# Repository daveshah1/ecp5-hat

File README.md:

# ecp5-hat

This board adds 64MB of SDRAM, 4-bit RGB+bright VGA output and a USB host connector to the Lattice [ECP5 Versa](http://www.latticesemi.com/Products/DevelopmentBoardsAndKits/ECP5VersaDevelopmentKit.aspx)
and [ECP5 Evaluation Board](http://www.latticesemi.com/en/Products/DevelopmentBoardsAndKits/ECP5EvaluationBoard)

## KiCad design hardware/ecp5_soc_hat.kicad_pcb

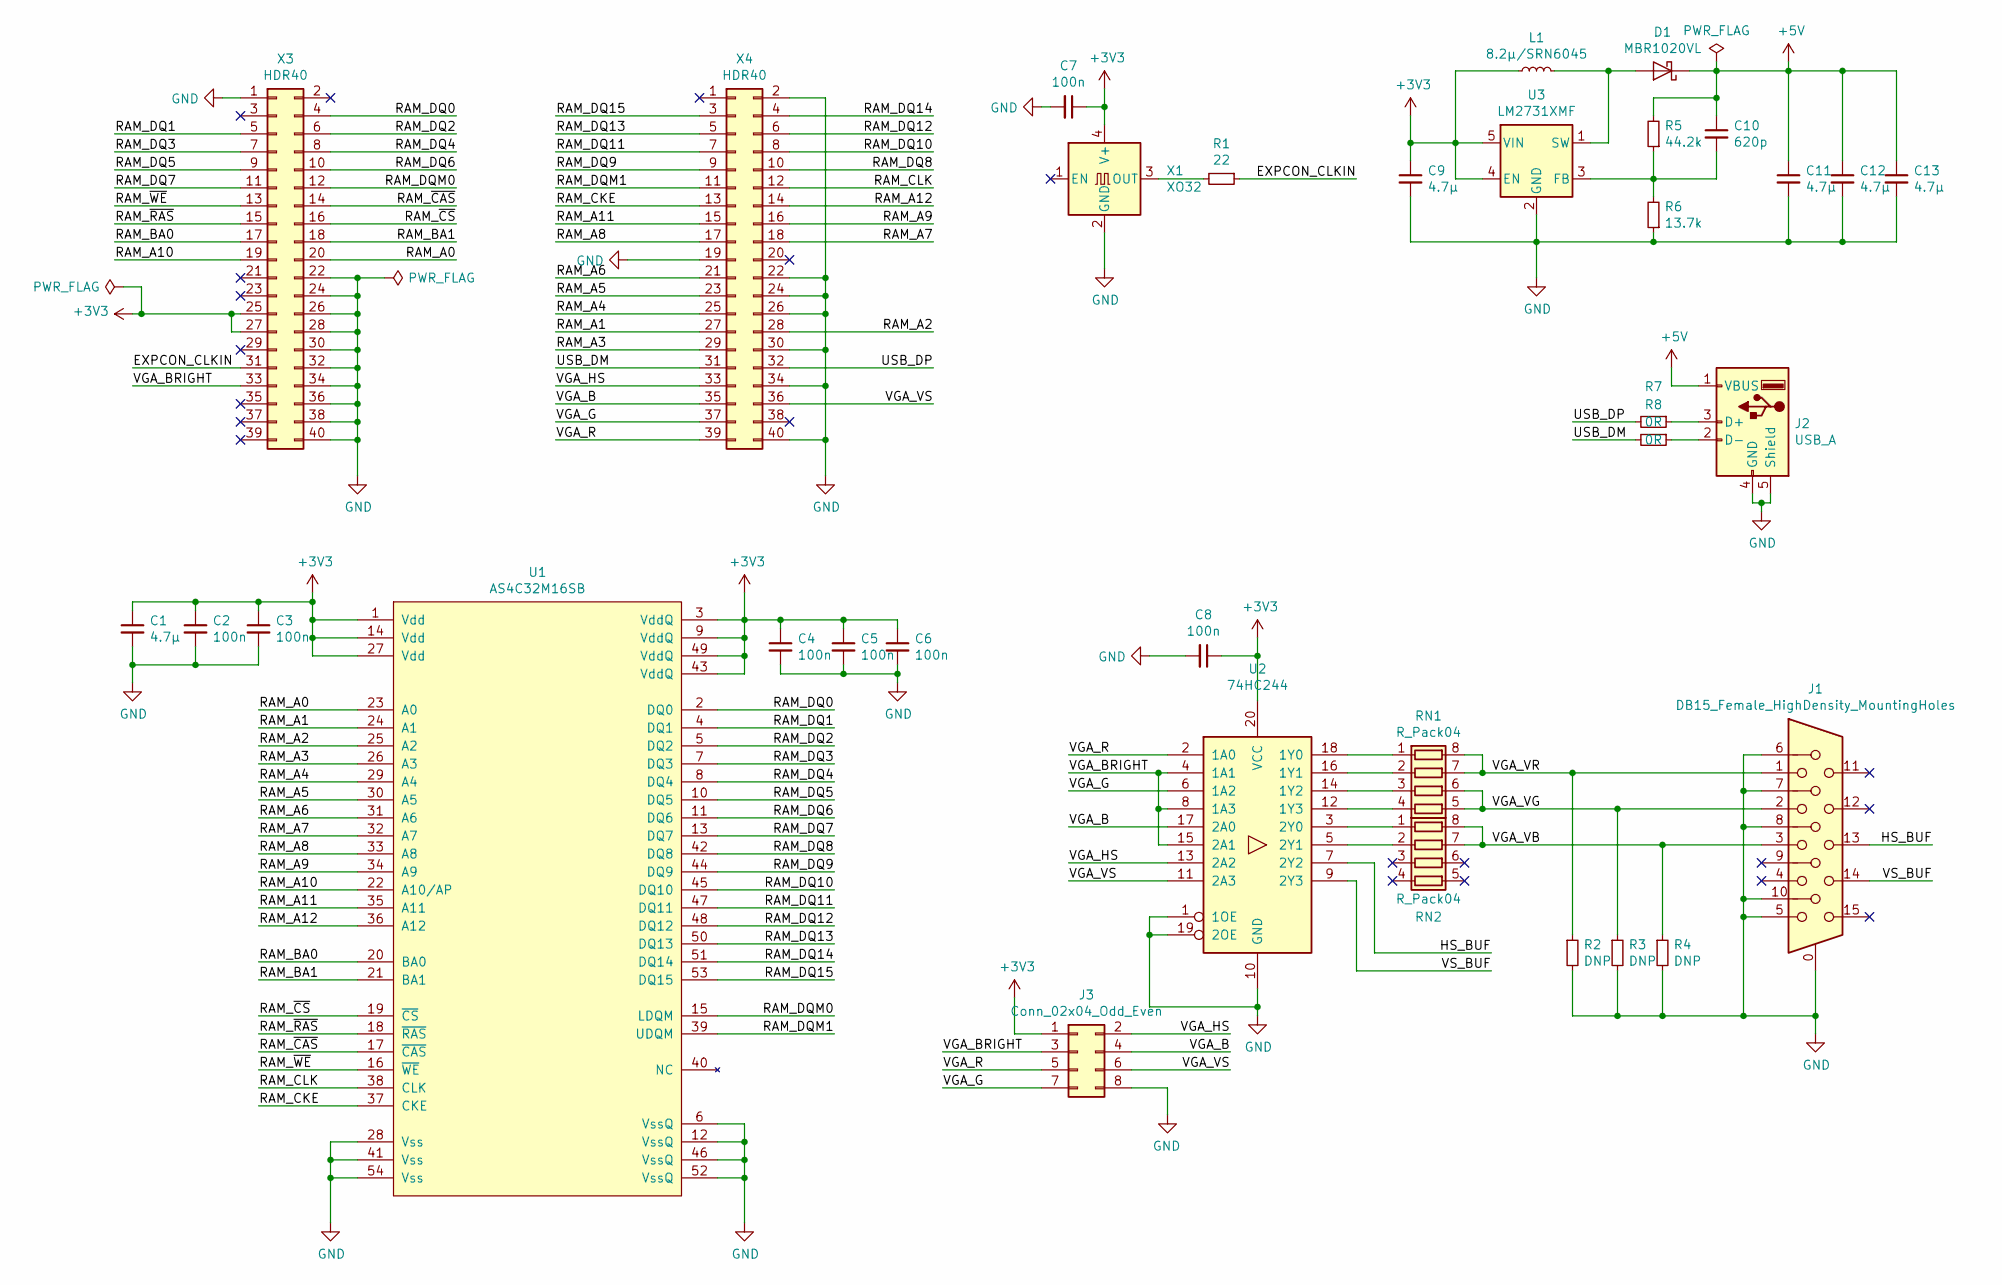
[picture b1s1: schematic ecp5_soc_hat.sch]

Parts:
C1, C9, C11, C12, C13: 4.7µ; C_0805_2012Metric_Pad1.15x1.40mm_HandSolder
C2, C3, C4, C5, C6, C7, C8: 100n; C_0402_1005Metric
C10: 620p; C_0402_1005Metric
D1: MBR1020VL; D_SOD-123F
J1: DB15_Female_HighDensity_MountingHoles; DSUB-15-HD_Female_Horizontal_P2.29x1.98mm_EdgePinOffset3.03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
J2: USB_A; 292303-7
J3: Conn_02x04_Odd_Even; PinHeader_2x04_P2.54mm_Vertical
L1: 8.2µ/SRN6045; SRN6045
R1: 22; R_0603_1608Metric_Pad1.05x0.95mm_HandSolder
R2, R3, R4: DNP; R_0603_1608Metric_Pad1.05x0.95mm_HandSolder
R5: 44.2k; R_0603_1608Metric_Pad1.05x0.95mm_HandSolder
R6: 13.7k; R_0603_1608Metric_Pad1.05x0.95mm_HandSolder
R7, R8: 0R; R_0603_1608Metric_Pad1.05x0.95mm_HandSolder
RN1, RN2: R_Pack04; R_Array_Convex_4x0402
U1: AS4C32M16SB; TSOP-II-54_22.2x10.16mm_P0.8mm
U2: 74HC244; SO-20_12.8x7.5mm_P1.27mm
U3: LM2731XMF; SOT-23-5
X1: XO32; Oscillator_SMD_EuroQuartz_XO32-4Pin_3.2x2.5mm
X3, X4: HDR40; PinSocket_2x20_P2.54mm_Vertical

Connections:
+3V3: C1.1, C2.1, C3.1, C4.1, C5.1, C6.1, C7.1, C8.1, C9.1, J3.1, L1.1, U1.1 (Vdd), U1.3 (VddQ), U1.9 (VddQ), U1.14 (Vdd), U1.27 (Vdd), U1.43 (VddQ), U1.49 (VddQ), U2.20 (VCC), U3.4 (EN), U3.5 (VIN), X1.4 (V+), X3.25, X3.27
+5V: C10.1, C11.1, C12.1, C13.1, D1.1 (K), J2.1 (VBUS), R5.2
/EXPCON_CLKIN: R1.1, X3.31
/EXPCON_OSC: X3.29
/HS_BUF: J1.13, U2.7 (2Y2)
/RAM_A0: U1.23 (A0), X3.20
/RAM_A1: U1.24 (A1), X4.27
/RAM_A2: U1.25 (A2), X4.28
/RAM_A3: U1.26 (A3), X4.29
/RAM_A4: U1.29 (A4), X4.25
/RAM_A5: U1.30 (A5), X4.23
/RAM_A6: U1.31 (A6), X4.21
/RAM_A7: U1.32 (A7), X4.18
/RAM_A8: U1.33 (A8), X4.17
/RAM_A9: U1.34 (A9), X4.16
/RAM_A10: U1.22 (A10/AP), X3.19
/RAM_A11: U1.35 (A11), X4.15
/RAM_A12: U1.36 (A12), X4.14
/RAM_BA0: U1.20 (BA0), X3.17
/RAM_BA1: U1.21 (BA1), X3.18
/RAM_CKE: U1.37 (CKE), X4.13
/RAM_CLK: U1.38 (CLK), X4.12
/RAM_DQ0: U1.2 (DQ0), X3.4
/RAM_DQ1: U1.4 (DQ1), X3.5
/RAM_DQ2: U1.5 (DQ2), X3.6
/RAM_DQ3: U1.7 (DQ3), X3.7
/RAM_DQ4: U1.8 (DQ4), X3.8
/RAM_DQ5: U1.10 (DQ5), X3.9
/RAM_DQ6: U1.11 (DQ6), X3.10
/RAM_DQ7: U1.13 (DQ7), X3.11
/RAM_DQ8: U1.42 (DQ8), X4.10
/RAM_DQ9: U1.44 (DQ9), X4.9
/RAM_DQ10: U1.45 (DQ10), X4.8
/RAM_DQ11: U1.47 (DQ11), X4.7
/RAM_DQ12: U1.48 (DQ12), X4.6
/RAM_DQ13: U1.50 (DQ13), X4.5
/RAM_DQ14: U1.51 (DQ14), X4.4
/RAM_DQ15: U1.53 (DQ15), X4.3
/RAM_DQM0: U1.15 (LDQM), X3.12
/RAM_DQM1: U1.39 (UDQM), X4.11
/RAM_~CAS: U1.17 (~CAS), X3.14
/RAM_~CS: U1.19 (~CS), X3.16
/RAM_~RAS: U1.18 (~RAS), X3.15
/RAM_~WE: U1.16 (~WE), X3.13
/USB_DM: R8.2, X4.31
/USB_DP: R7.2, X4.32
/VGA_B: J3.4, U2.17 (2A0), X4.35
/VGA_BRIGHT: J3.3, U2.4 (1A1), U2.8 (1A3), U2.15 (2A1), X3.33
/VGA_G: J3.7, U2.6 (1A2), X4.37
/VGA_HS: J3.2, U2.13 (2A2), X4.33
/VGA_R: J3.5, U2.2 (1A0), X4.39
/VGA_VB: J1.3, R4.1, RN2.7 (R2.2), RN2.8 (R1.2)
/VGA_VG: J1.2, R3.1, RN1.5 (R4.2), RN1.6 (R3.2)
/VGA_VR: J1.1, R2.1, RN1.7 (R2.2), RN1.8 (R1.2)
/VGA_VS: J3.6, U2.11 (2A3), X4.36
/VS_BUF: J1.14, U2.9 (2Y3)
GND: C1.2, C2.2, C3.2, C4.2, C5.2, C6.2, C7.2, C8.2, C9.2, C11.2, C12.2, C13.2, J1.0, J1.5, J1.6, J1.7, J1.8, J1.10, J2.4 (GND), J2.5 (Shield), J3.8, R2.2, R3.2, R4.2, R6.1, U1.6 (VssQ), U1.12 (VssQ), U1.28 (Vss), U1.41 (Vss), U1.46 (VssQ), U1.52 (VssQ), U1.54 (Vss), U2.1 (1OE), U2.10 (GND), U2.19 (2OE), U3.2 (GND), X1.2 (GND), X3.1, X3.22, X3.24, X3.26, X3.28, X3.30, X3.32, X3.34, X3.36, X3.38, X3.40, X4.2, X4.19, X4.22, X4.24, X4.26, X4.30, X4.34, X4.40
unnamed: C10.2, R5.1, R6.2, U3.3 (FB)
unnamed: D1.2 (A), L1.2, U3.1 (SW)
unnamed: J2.2 (D-), R8.1
unnamed: J2.3 (D+), R7.1
unnamed: R1.2, X1.3 (OUT)
unnamed: RN1.1 (R1.1), U2.18 (1Y0)
unnamed: RN1.2 (R2.1), U2.16 (1Y1)
unnamed: RN1.3 (R3.1), U2.14 (1Y2)
unnamed: RN1.4 (R4.1), U2.12 (1Y3)
unnamed: RN2.1 (R1.1), U2.3 (2Y0)
unnamed: RN2.2 (R2.1), U2.5 (2Y1)

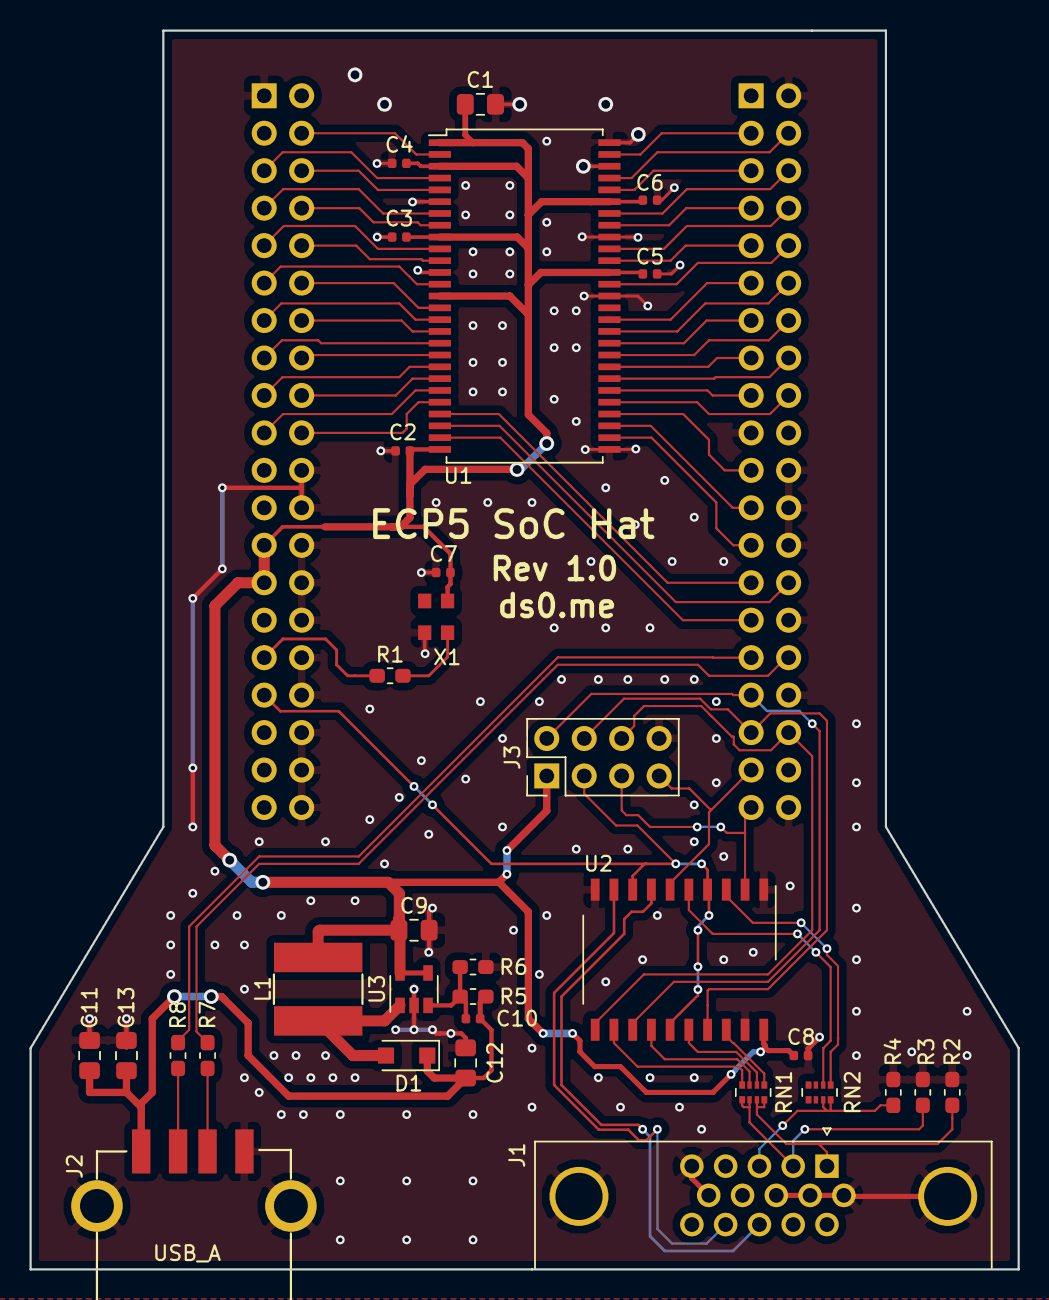
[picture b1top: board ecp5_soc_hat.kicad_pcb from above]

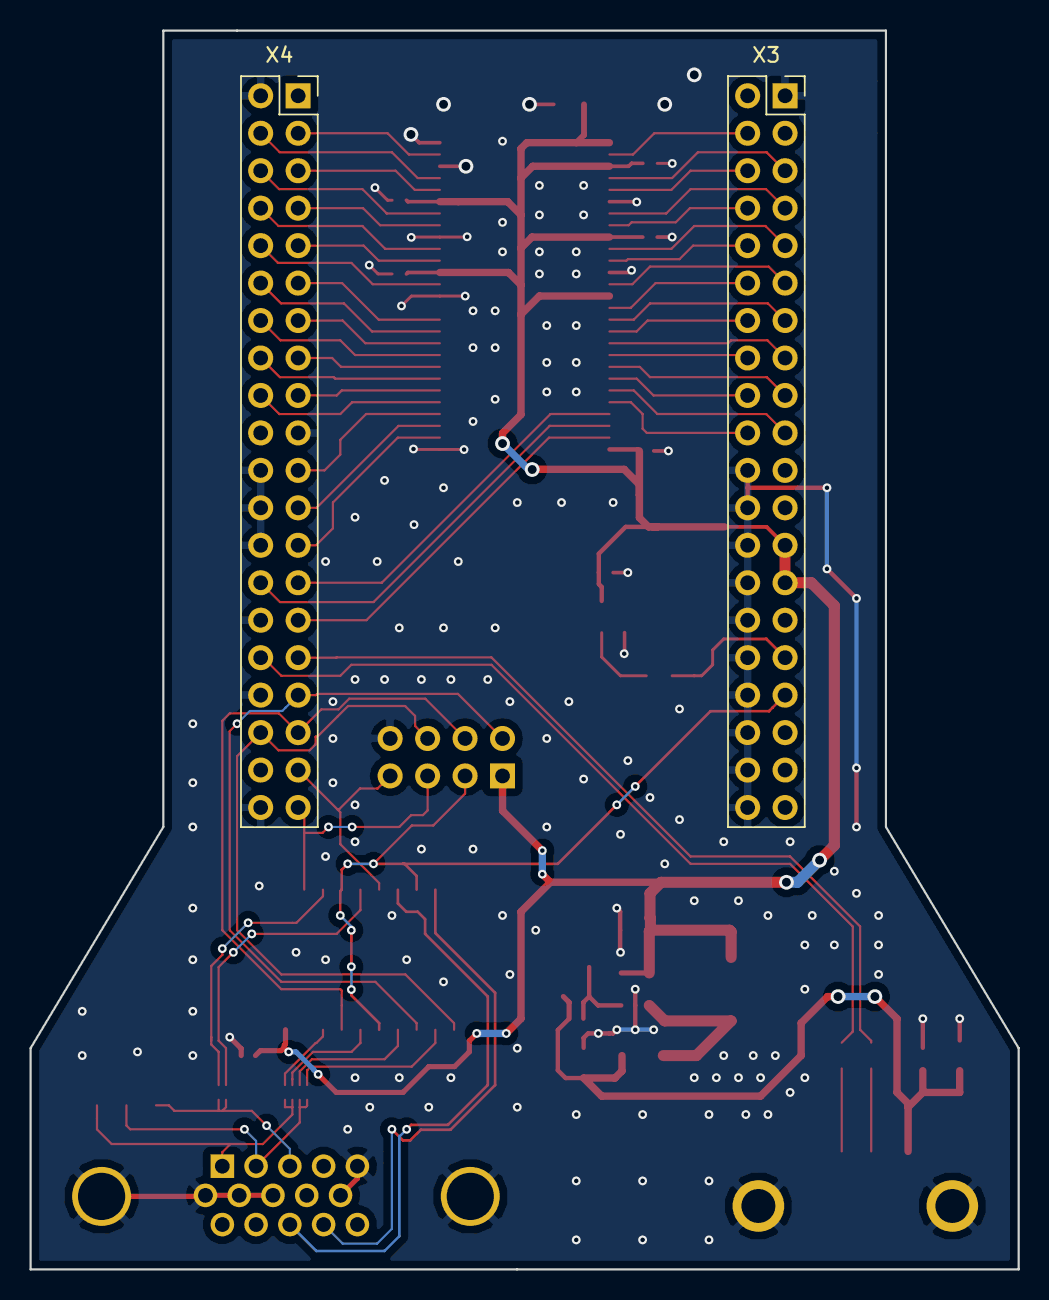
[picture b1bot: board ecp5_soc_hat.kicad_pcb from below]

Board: 2 copper layers, 67.0 x 84.0 mm, 34 parts (2 on the bottom side), 67 nets.

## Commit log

2018-10-20 Initial schematics
2018-10-20 Initial PCB placement
2018-10-20 PCB fully routed
2018-10-20 Tidy up board
2018-10-31 Production PCBs rev1.0
2018-10-31 Create LICENSE
